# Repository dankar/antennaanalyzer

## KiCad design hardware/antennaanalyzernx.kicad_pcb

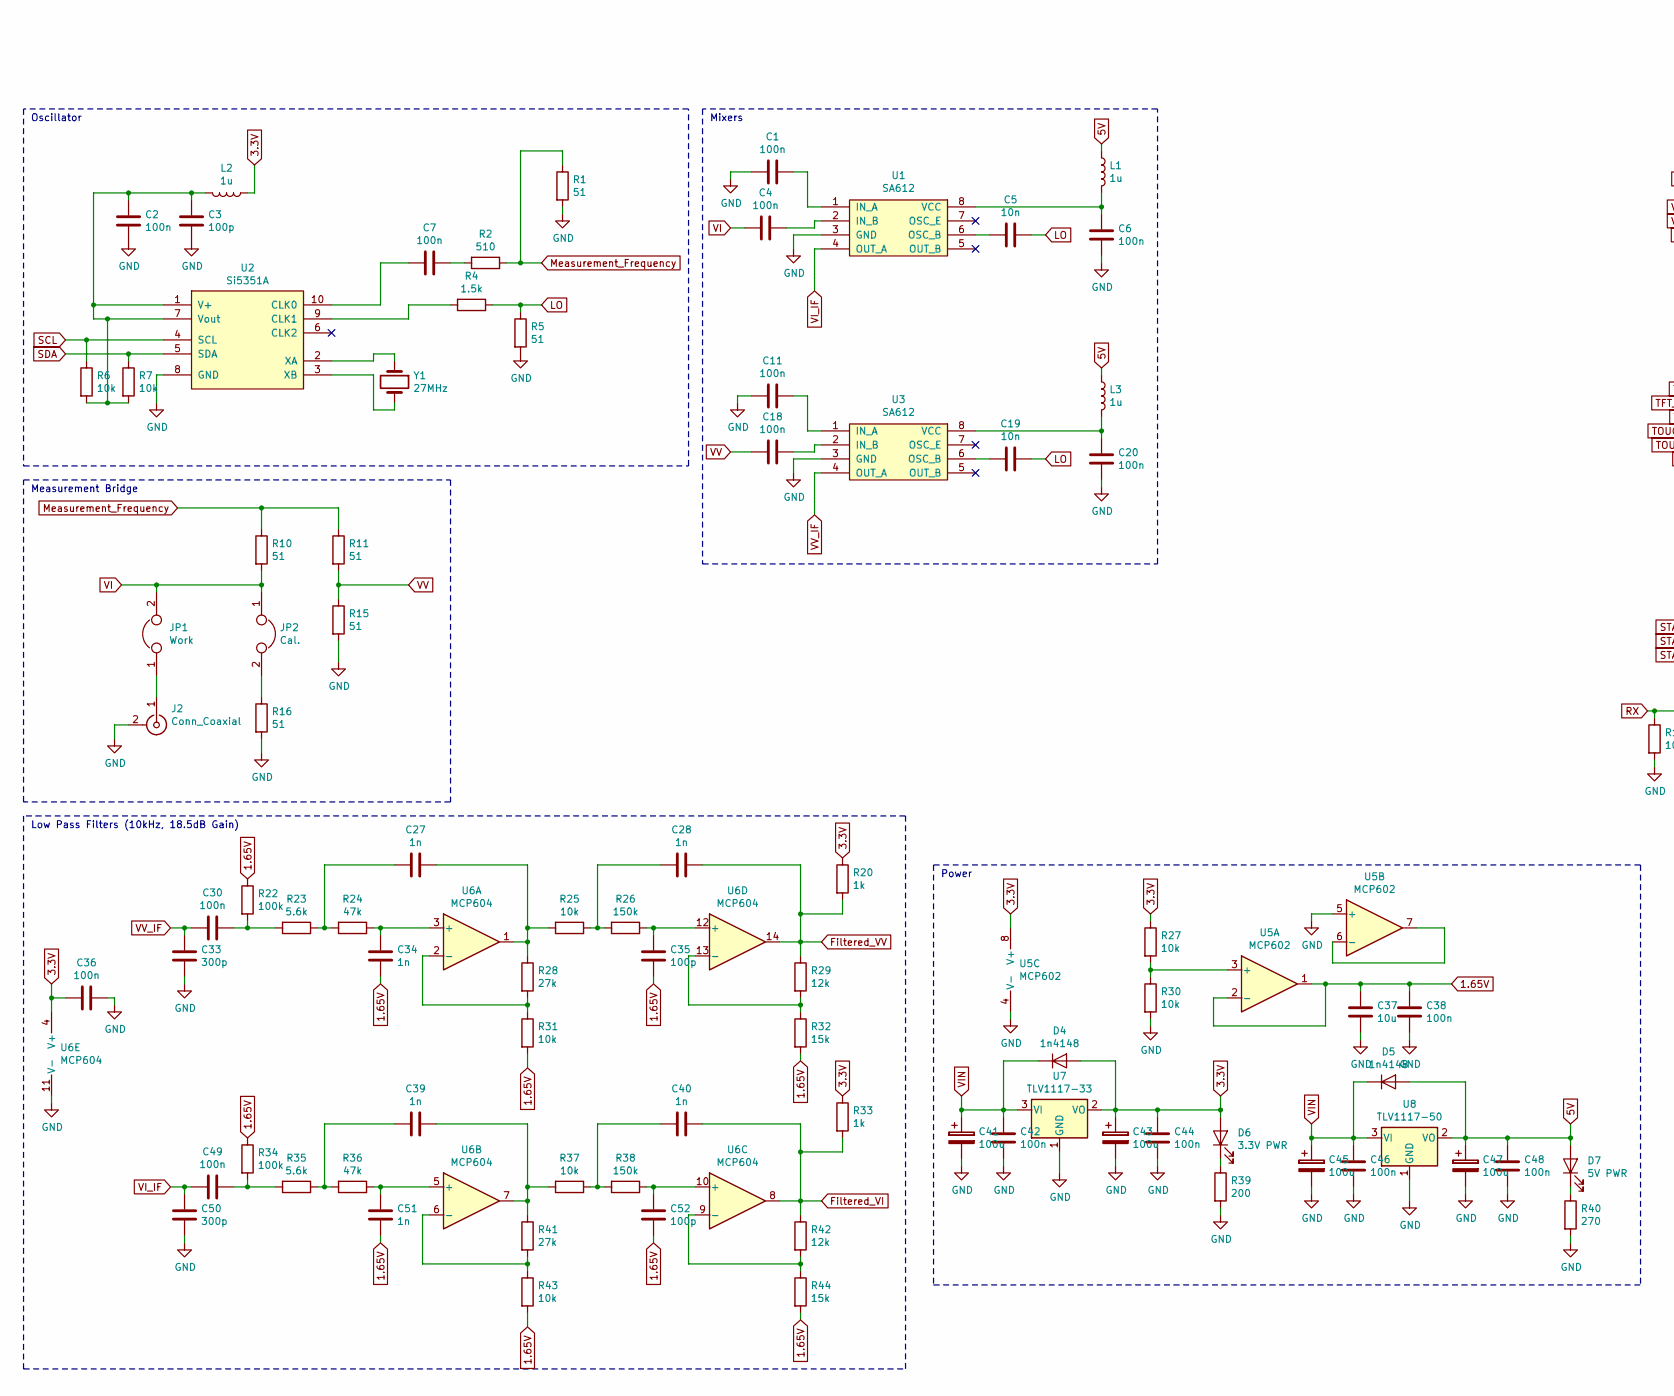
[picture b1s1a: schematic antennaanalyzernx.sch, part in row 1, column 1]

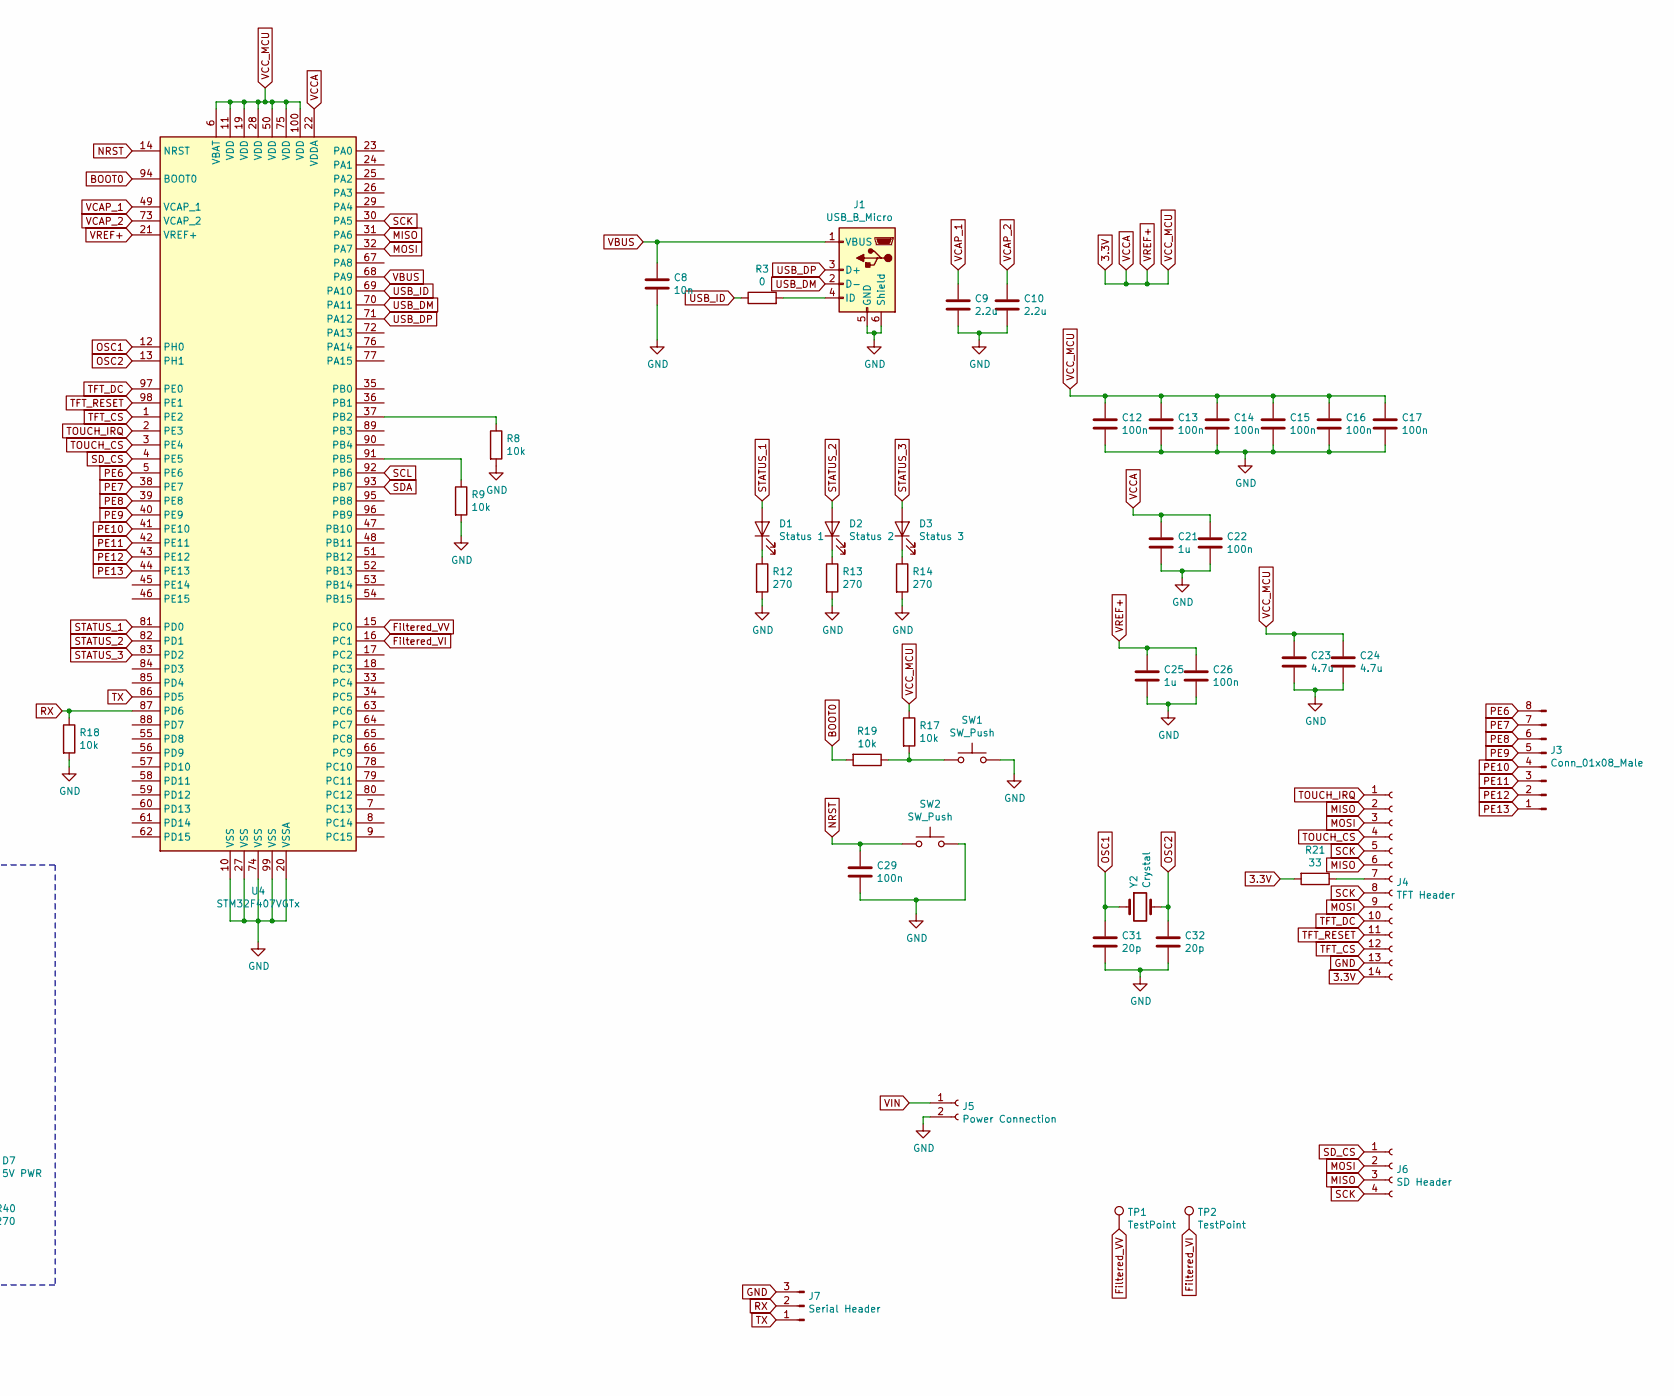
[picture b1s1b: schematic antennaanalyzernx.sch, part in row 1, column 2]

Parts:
C1, C2, C4, C6, C7, C11, C12, C13, C14, C15, C16, C17, C18, C20, C22, C26, C29, C30, C36, C38, C42, C44, C46, C48, C49: 100n; C_0805_HandSoldering
C3, C35, C52: 100p; C_0805_HandSoldering
C5, C8, C19: 10n; C_0805_HandSoldering
C9, C10: 2.2u; C_0805_HandSoldering
C21, C25: 1u; C_0805_HandSoldering
C23, C24: 4.7u; C_0805_HandSoldering
C27, C28, C34, C39, C40, C51: 1n; C_0805_HandSoldering
C31, C32: 20p; C_0805_HandSoldering
C33, C50: 300p; C_0805_HandSoldering
C37: 10u; C_0805_HandSoldering
C41, C43, C45, C47: 100u; CP_Elec_6.3x5.3
D1: Status 1; LED_0805_HandSoldering
D2: Status 2; LED_0805_HandSoldering
D3: Status 3; LED_0805_HandSoldering
D4, D5: 1n4148; D_SOD-323
D6: 3.3V PWR; LED_0805_HandSoldering
D7: 5V PWR; LED_0805_HandSoldering
J1: USB_B_Micro; USB Micro
J2: Conn_Coaxial; CON-SMA-EDGE
J3: Conn_01x08_Male; Pin_Header_Straight_1x08_Pitch2.54mm
J4: TFT Header; Pin_Header_Straight_1x14_Pitch2.54mm
J5: Power Connection; Pin_Header_Straight_1x02_Pitch2.54mm
J6: SD Header; Pin_Header_Straight_1x04_Pitch2.54mm
J7: Serial Header; Pin_Header_Straight_1x03_Pitch2.54mm
JP1: Work; Pin_Header_Straight_1x02_Pitch2.54mm
JP2: Cal.; Pin_Header_Straight_1x02_Pitch2.54mm
L1, L2, L3: 1u; L_1210_HandSoldering
R1, R5, R10, R11, R15, R16: 51; R_0805_HandSoldering
R2: 510; R_0805_HandSoldering
R3: 0; R_0805_HandSoldering
R4: 1.5k; R_0805_HandSoldering
R6, R7, R8, R9, R17, R18, R19, R25, R27, R30, R31, R37, R43: 10k; R_0805_HandSoldering
R12, R13, R14, R40: 270; R_0805_HandSoldering
R20, R33: 1k; R_0805_HandSoldering
R21: 33; R_0805_HandSoldering
R22, R34: 100k; R_0805_HandSoldering
R23, R35: 5.6k; R_0805_HandSoldering
R24, R36: 47k; R_0805_HandSoldering
R26, R38: 150k; R_0805_HandSoldering
R28, R41: 27k; R_0805_HandSoldering
R29, R42: 12k; R_0805_HandSoldering
R32, R44: 15k; R_0805_HandSoldering
R39: 200; R_0805_HandSoldering
SW1, SW2: SW_Push; Switch
TP1, TP2: TestPoint; Measurement_Point_Round-SMD-Pad_Small
U1, U3: SA612; SOIC-8_3.9x4.9mm_Pitch1.27mm
U2: Si5351A; MSOP-10_3x3mm_Pitch0.5mm
U4: STM32F407VGTx; LQFP-100_14x14mm_Pitch0.5mm
U5: MCP602; SOIC-8_3.9x4.9mm_Pitch1.27mm
U6: MCP604; SOIC-14_3.9x8.7mm_Pitch1.27mm
U7: TLV1117-33; SOT-223-3_TabPin2
U8: TLV1117-50; SOT-223-3_TabPin2
Y1: 27MHz; Crystal_HC49-U_Vertical
Y2: Crystal; Crystal_HC49-U_Vertical

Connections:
1.65V: C34.2, C35.2, C37.1, C38.1, C51.2, C52.2, R22.1, R31.2, R32.2, R34.1, R43.2, R44.2, U5.1, U5.2 (-)
3.3V: C12.1, C13.1, C14.1, C15.1, C16.1, C17.1, C21.1, C22.1, C23.1, C24.1, C25.1, C26.1, C36.2, C43.1, C44.1, D4.2 (A), D6.2 (A), J4.14, L2.1, R17.1, R20.1, R21.2, R27.1, R33.1, U4.6 (VBAT), U4.11 (VDD), U4.19 (VDD), U4.21 (VREF+), U4.22 (VDDA), U4.28 (VDD), U4.50 (VDD), U4.75 (VDD), U4.100 (VDD), U5.8 (V+), U6.4 (V+), U7.2 (VO)
5V: C47.1, C48.1, D5.2 (A), D7.2 (A), L1.1, L3.1, U8.2 (VO)
BOOT0: R19.2, U4.94 (BOOT0)
Filtered_VI: C40.1, R33.2, R42.1, TP2.1, U4.16 (PC1), U6.8
Filtered_VV: C28.1, R20.2, R29.1, TP1.1, U4.15 (PC0), U6.14
GND: C1.2, C2.2, C3.2, C6.2, C8.2, C9.2, C10.2, C11.2, C12.2, C13.2, C14.2, C15.2, C16.2, C17.2, C20.2, C21.2, C22.2, C23.2, C24.2, C25.2, C26.2, C29.2, C31.2, C32.2, C33.2, C36.1, C37.2, C38.2, C41.2, C42.2, C43.2, C44.2, C45.2, C46.2, C47.2, C48.2, C50.2, J1.5 (GND), J1.6 (Shield), J2.2 (Ext), J4.13, J5.2, J7.3, R1.2, R5.2, R8.2, R9.2, R12.2, R13.2, R14.2, R15.2, R16.2, R18.2, R30.2, R39.2, R40.2, SW1.2, SW2.2, U1.3 (GND), U2.8 (GND), U3.3 (GND), U4.10 (VSS), U4.20 (VSSA), U4.27 (VSS), U4.74 (VSS), U4.99 (VSS), U5.4 (V-), U5.5 (+), U6.11 (V-), U7.1 (GND), U8.1 (GND)
LO: C5.1, C19.1, R4.1, R5.1
MISO: J4.2, J4.6, J6.3, U4.31 (PA6)
MOSI: J4.3, J4.9, J6.2, U4.32 (PA7)
Measurement_Frequency: R1.1, R2.1, R10.1, R11.1
NRST: C29.1, SW2.1, U4.14 (NRST)
unnamed: C1.1, U1.1 (IN_A)
unnamed: C2.1, C3.1, L2.2, R6.2, R7.2, U2.1 (V+), U2.7 (Vout)
unnamed: C4.1, U1.2 (IN_B)
unnamed: C5.2, U1.6 (OSC_B)
unnamed: C6.1, L1.2, U1.8 (VCC)
unnamed: C7.1, R2.2
unnamed: C7.2, U2.10 (CLK0)
unnamed: C11.1, U3.1 (IN_A)
unnamed: C18.1, U3.2 (IN_B)
unnamed: C19.2, U3.6 (OSC_B)
unnamed: C20.1, L3.2, U3.8 (VCC)
unnamed: C27.1, R25.2, R28.1, U6.1
unnamed: C27.2, R23.1, R24.2
unnamed: C28.2, R25.1, R26.2
unnamed: C30.1, R22.2, R23.2
unnamed: C34.1, R24.1, U6.3 (+)
unnamed: C35.1, R26.1, U6.12 (+)
unnamed: C39.1, R37.2, R41.1, U6.7
unnamed: C39.2, R35.1, R36.2
unnamed: C40.2, R37.1, R38.2
unnamed: C49.1, R34.2, R35.2
unnamed: C51.1, R36.1, U6.5 (+)
unnamed: C52.1, R38.1, U6.10 (+)
unnamed: D1.1 (K), R12.1
unnamed: D2.1 (K), R13.1
unnamed: D3.1 (K), R14.1
unnamed: D6.1 (K), R39.1
unnamed: D7.1 (K), R40.1
unnamed: J1.4 (ID), R3.2
unnamed: J2.1 (In), JP1.1
unnamed: J4.7, R21.1
unnamed: JP2.2, R16.1
unnamed: R4.2, U2.9 (CLK1)
unnamed: R8.1, U4.37 (PB2)
unnamed: R9.1, U4.91 (PB5)
unnamed: R17.2, R19.1, SW1.1
unnamed: R27.2, R30.1, U5.3 (+)
unnamed: R28.2, R31.1, U6.2 (-)
unnamed: R29.2, R32.1, U6.13 (-)
unnamed: R41.2, R43.1, U6.6 (-)
unnamed: R42.2, R44.1, U6.9 (-)
unnamed: U2.2 (XA), Y1.1
unnamed: U2.3 (XB), Y1.2
unnamed: U5.6 (-), U5.7
OSC1: C31.1, U4.12 (PH0), Y2.1
OSC2: C32.1, U4.13 (PH1), Y2.2
PE6: J3.8, U4.5 (PE6)
PE7: J3.7, U4.38 (PE7)
PE8: J3.6, U4.39 (PE8)
PE9: J3.5, U4.40 (PE9)
PE10: J3.4, U4.41 (PE10)
PE11: J3.3, U4.42 (PE11)
PE12: J3.2, U4.43 (PE12)
PE13: J3.1, U4.44 (PE13)
RX: J7.2, R18.1, U4.87 (PD6)
SCK: J4.5, J4.8, J6.4, U4.30 (PA5)
SCL: R6.1, U2.4 (SCL), U4.92 (PB6)
SDA: R7.1, U2.5 (SDA), U4.93 (PB7)
SD_CS: J6.1, U4.4 (PE5)
STATUS_1: D1.2 (A), U4.81 (PD0)
STATUS_2: D2.2 (A), U4.82 (PD1)
STATUS_3: D3.2 (A), U4.83 (PD2)
TFT_CS: J4.12, U4.1 (PE2)
TFT_DC: J4.10, U4.97 (PE0)
TFT_RESET: J4.11, U4.98 (PE1)
TOUCH_CS: J4.4, U4.3 (PE4)
TOUCH_IRQ: J4.1, U4.2 (PE3)
TX: J7.1, U4.86 (PD5)
USB_DM: J1.2 (D-), U4.70 (PA11)
USB_DP: J1.3 (D+), U4.71 (PA12)
USB_ID: R3.1, U4.69 (PA10)
VBUS: C8.1, J1.1 (VBUS), U4.68 (PA9)
VCAP_1: C9.1, U4.49 (VCAP_1)
VCAP_2: C10.1, U4.73 (VCAP_2)
VI: C4.2, JP1.2, JP2.1, R10.2
VIN: C41.1, C42.1, C45.1, C46.1, D4.1 (K), D5.1 (K), J5.1, U7.3 (VI), U8.3 (VI)
VI_IF: C49.2, C50.1, U1.4 (OUT_A)
VV: C18.2, R11.2, R15.1
VV_IF: C30.2, C33.1, U3.4 (OUT_A)

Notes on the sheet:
Oscillator
Measurement Bridge
Mixers
Low Pass Filters (10kHz, 18.5dB Gain)
Power

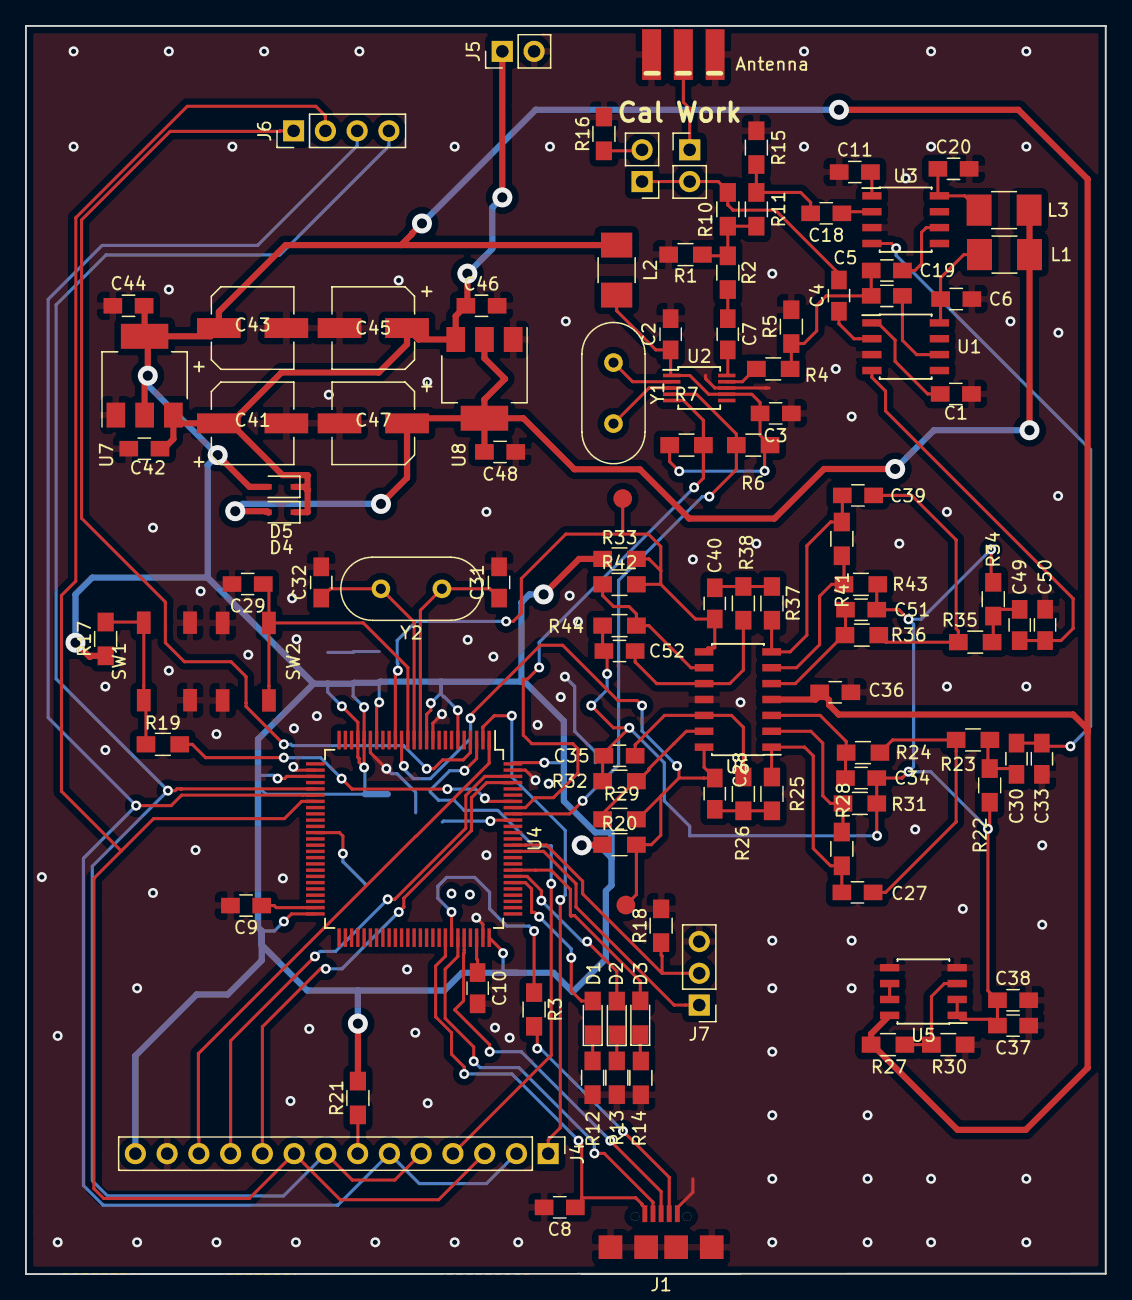
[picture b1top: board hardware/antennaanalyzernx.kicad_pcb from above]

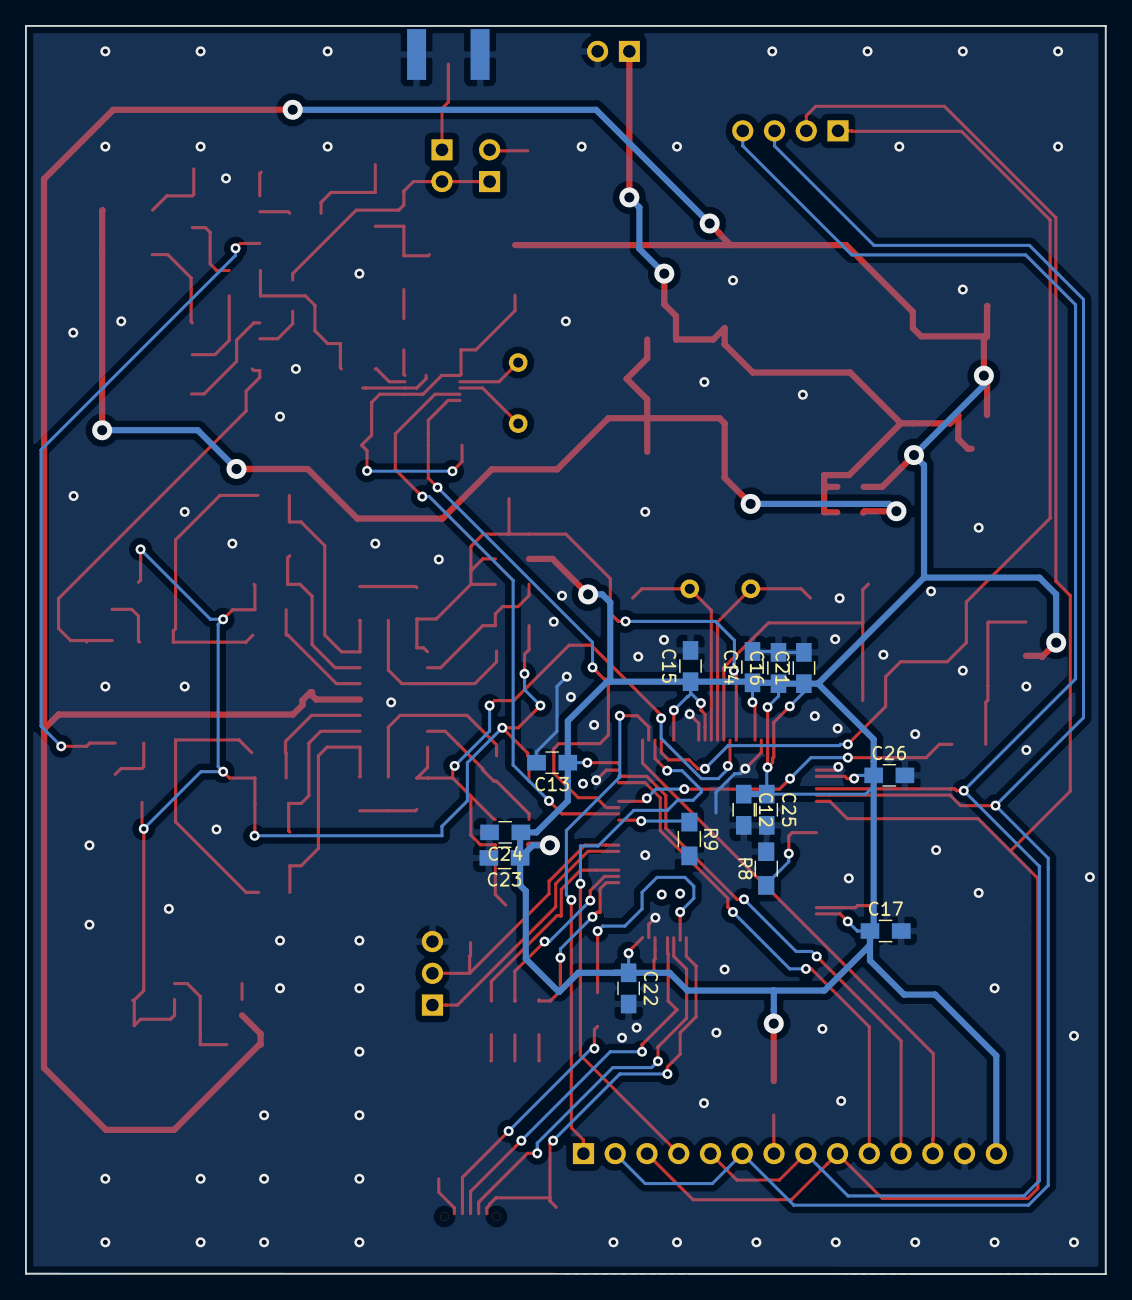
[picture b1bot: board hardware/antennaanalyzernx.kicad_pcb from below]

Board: 2 copper layers, 86.4 x 99.8 mm, 124 parts (14 on the bottom side), 81 nets.

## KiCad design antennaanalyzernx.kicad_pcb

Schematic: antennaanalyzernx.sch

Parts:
C1, C2, C3, C5, C7, C8, C10, C12, C13, C16, C18, C19, C20, C21, C25, C26, C27, C31, C32, C34, C40, C42, C43, C45, C47, C48: 100n; C_0805_HandSoldering
C4, C30, C51: 100p; C_0805_HandSoldering
C6, C17: 10n; C_0805_HandSoldering
C9, C14, C33: 10u; C_0805_HandSoldering
C22: 1u; C_0805_HandSoldering
C23, C24, C29, C37, C38, C50: 1n; C_0805_HandSoldering
C28, C49: 300p; C_0805_HandSoldering
C35, C36: 22p; C_0805_HandSoldering
C39, C41, C44, C46: 100u; CP_Elec_6.3x5.3
D1, D2, D3, D4: 1n4148; D_SOD-323
D5: 3.3V PWR; LED_0805_HandSoldering
D6: 5V PWR; LED_0805_HandSoldering
D7: Status 1; LED_0805_HandSoldering
D8: Status 2; LED_0805_HandSoldering
D9: Status 3; LED_0805_HandSoldering
J1: Power Connection; Molex_KK-6410-02_02x2.54mm_Straight
J2: SPI Header; Molex_KK-6410-04_04x2.54mm_Straight
J3: Serial Header; Molex_KK-6410-06_06x2.54mm_Straight
J4: GPIO; Molex_KK-6410-04_04x2.54mm_Straight
J5: Conn_Coaxial; CON-SMA-EDGE
J6: TFT Connection; Molex_KK-6410-09_09x2.54mm_Straight
J7: Touch Connection; Molex_KK-6410-05_05x2.54mm_Straight
J8: SD Connection; Molex_KK-6410-04_04x2.54mm_Straight
JP1: Work; Pin_Header_Straight_1x02_Pitch2.54mm
JP2: Cal.; Pin_Header_Straight_1x02_Pitch2.54mm
L1, L2, L3, L4: 1u; L_1210_HandSoldering
R1, R3, R6, R8, R9, R10, R19, R21, R24, R25, R30, R34, R37, R39, R40: 10k; R_0805_HandSoldering
R2, R7, R11, R12, R14, R15: 51; R_0805_HandSoldering
R4: 510; R_0805_HandSoldering
R5: 1.5k; R_0805_HandSoldering
R13, R41, R42: 1k; R_0805_HandSoldering
R16, R27: 100k; R_0805_HandSoldering
R17, R28: 5.6k; R_0805_HandSoldering
R18, R29: 47k; R_0805_HandSoldering
R20, R31: 150k; R_0805_HandSoldering
R22, R35: 27k; R_0805_HandSoldering
R23, R36: 12k; R_0805_HandSoldering
R26, R38: 15k; R_0805_HandSoldering
R32: 200; R_0805_HandSoldering
R33, R43, R44, R45: 270; R_0805_HandSoldering
RV1, RV2, RV3: 100k; Potentiometer_Trimmer_Bourns_3266W
SW1: Reset; Switch
TP1: VV Test Point; Measurement_Point_Round-SMD-Pad_Small
TP2, TP3, TP4, TP5: TestPoint; Measurement_Point_Round-SMD-Pad_Small
U1, U4: SA612; SOIC-8_3.9x4.9mm_Pitch1.27mm
U2, U5, U8: LM358; SOIC-8_3.9x4.9mm_Pitch1.27mm
U3: Si5351A; MSOP-10_3x3mm_Pitch0.5mm
U6: 74HC86; SOIC-14_3.9x8.7mm_Pitch1.27mm
U7: 74HC74; SOIC-14_3.9x8.7mm_Pitch1.27mm
U9: LM324; SOIC-14_3.9x8.7mm_Pitch1.27mm
U10: TLV1117-33; SOT-223-3_TabPin2
U11: TLV1117-50; SOT-223-3_TabPin2
U12: ATmega1284P-AU; TQFP-44_10x10mm_Pitch0.8mm
Y1: 27MHz; Crystal_HC49-U_Vertical
Y2: 16MHz; Crystal_HC49-U_Vertical

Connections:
2.5V: C29.2, C30.2, C33.1, C34.1, C50.2, C51.2, R16.1, R25.2, R26.2, R27.1, R37.2, R38.2, U5.2 (-), U5.6 (-), U8.1, U8.2 (-)
3.3V: C41.1, C42.1, D3.2 (A), D5.2 (A), L2.1, U10.2 (VO)
5V: C8.2, C19.2, C20.2, C21.2, C25.1, C32.2, C46.1, C47.1, D4.2 (A), D6.2 (A), J3.3, J6.9, L1.1, L3.1, L4.1, R21.1, R34.2, R41.1, R42.1, U2.8 (V+), U5.8 (V+), U6.14, U7.1, U7.4, U7.10, U7.13, U7.14, U8.8 (V+), U9.4 (V+), U11.2 (VO), U12.5, U12.17, U12.38
CTS: C3.2, C4.2, C5.2, C7.2, C8.1, C9.2, C13.2, C14.2, C18.2, C19.1, C20.1, C21.1, C22.2, C25.2, C27.2, C28.2, C31.2, C32.1, C33.2, C34.2, C35.1, C36.1, C39.2, C40.2, C41.2, C42.2, C44.2, C45.2, C46.2, C47.2, C49.2, J1.2, J3.1, J3.2, J5.2 (Ext), J6.8, R1.1, R2.2, R3.2, R6.1, R7.2, R10.2, R14.2, R15.2, R24.2, R32.2, R33.2, R43.2, R44.2, R45.2, RV1.3, RV2.3, RV3.3, SW1.2, U1.3, U2.4 (V-), U3.8, U4.3, U5.4 (V-), U6.4, U6.5, U6.7, U6.9, U6.10, U6.12, U6.13, U7.7, U7.11, U7.12, U8.4 (V-), U8.5 (+), U9.11 (V-), U10.1 (GND), U11.1 (GND), U12.6, U12.18, U12.28, U12.39
Capacitive_Sign: U7.5, U12.21
DTR: C43.1, J3.6
Filtered_VI: C12.2, C38.1, R36.1, R42.2, TP5.1, U5.5 (+), U9.14
Filtered_VV: C2.2, C24.1, R23.1, R41.2, TP4.1, U5.3 (+), U9.7
GPIO20: J4.1, U12.23
GPIO21: J4.2, U12.24
GPIO22: J4.3, U12.25
GPIO23: J4.4, U12.26
Inductive_Sign: U7.6, U12.22
LO: C6.1, C17.1, R5.1, R7.1
MISO: J2.2, J6.1, J7.2, J8.3, U12.2
MOSI: J2.3, J6.4, J7.3, J8.2, U12.1
Measurement_Frequency: R2.1, R4.1, R11.1, R12.1
unnamed: C1.1, U1.2
unnamed: C2.1, R1.2, R39.2
unnamed: C3.1, C4.1, L2.2, R8.2, R9.2, U3.1, U3.7
unnamed: C5.1, U1.1
unnamed: C6.2, U1.6
unnamed: C7.1, L1.2, U1.8
unnamed: C9.1, D1.1 (K), R3.1, RV1.1, U2.2 (-)
unnamed: C10.1, R4.2
unnamed: C10.2, U3.10
unnamed: C12.1, R6.2, R40.2
unnamed: C13.1, U4.1
unnamed: C14.1, D2.1 (K), R10.1, RV2.1, U2.6 (-)
unnamed: C16.1, U4.2
unnamed: C17.2, U4.6
unnamed: C18.1, L3.2, U4.8
unnamed: C22.1, R13.1, RV3.1
unnamed: C23.1, R19.2, R22.1, U9.1
unnamed: C23.2, R17.1, R18.2
unnamed: C24.2, R19.1, R20.2
unnamed: C26.1, R16.2, R17.2
unnamed: C27.1, L4.2, U12.27
unnamed: C29.1, R18.1, U9.3 (+)
unnamed: C30.1, R20.1, U9.5 (+)
unnamed: C31.1, U12.29
unnamed: C35.2, U12.7, Y2.1
unnamed: C36.2, U12.8, Y2.2
unnamed: C37.1, R30.2, R35.1, U9.8
unnamed: C37.2, R28.1, R29.2
unnamed: C38.2, R30.1, R31.2
unnamed: C48.1, R27.2, R28.2
unnamed: C50.1, R29.1, U9.10 (+)
unnamed: C51.1, R31.1, U9.12 (+)
unnamed: D1.2 (A), U2.1
unnamed: D2.2 (A), U2.7
unnamed: D5.1 (K), R32.1
unnamed: D6.1 (K), R33.1
unnamed: D7.1 (K), R43.1
unnamed: D8.1 (K), R44.1
unnamed: D9.1 (K), R45.1
unnamed: J5.1 (In), JP1.1
unnamed: JP2.2, R15.1
unnamed: R5.2, U3.9
unnamed: R13.2, U6.3
unnamed: R21.2, R24.1, U8.3 (+)
unnamed: R22.2, R25.1, U9.2 (-)
unnamed: R23.2, R26.1, U9.6 (-)
unnamed: R35.2, R37.1, U9.9 (-)
unnamed: R36.2, R38.1, U9.13 (-)
unnamed: R39.1, U2.3 (+)
unnamed: R40.1, U2.5 (+)
unnamed: U3.2, Y1.1
unnamed: U3.3, Y1.2
unnamed: U5.1, U6.1, U7.3
unnamed: U5.7, U6.2, U7.2
unnamed: U8.6 (-), U8.7
Phase: RV3.2, TP3.1, U12.35
RESET: C43.2, J2.4, R34.1, SW1.1, U12.4
RX: J3.4, U12.9
SCK: J2.1, J6.3, J7.5, J8.4, U12.3
SCL: R8.1, U3.4, U12.19
SDA: R9.1, U3.5, U12.20
SD_CS: J8.1, U12.13
STATUS_1: D7.2 (A), U12.14
STATUS_2: D8.2 (A), U12.15
STATUS_3: D9.2 (A), U12.16
TFT_CS: J6.7, U12.42
TFT_DC: J6.5, U12.40
TFT_LED: J6.2, U12.43
TFT_RESET: J6.6, U12.41
TOUCH_CS: J7.4, U12.12
TOUCH_IRQ: J7.1, U12.11
TX: J3.5, U12.10
VI: C1.2, JP1.2, JP2.1, R11.2
VIN: C39.1, C40.1, C44.1, C45.1, D3.1 (K), D4.1 (K), J1.1, U10.3 (VI), U11.3 (VI)
VI_IF: C48.2, C49.1, U1.4
VI_Peak: RV2.2, TP2.1, U12.36
VV: C16.2, R12.2, R14.1
VV_IF: C26.2, C28.1, U4.4
VV_Peak: RV1.2, TP1.1, U12.37

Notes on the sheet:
Oscillator
Measurement Bridge
Mixers
Low Pass Filters (10kHz, 18.5dB Gain)
Peak Detectors
Phase Detector
Connections
Power
MCU

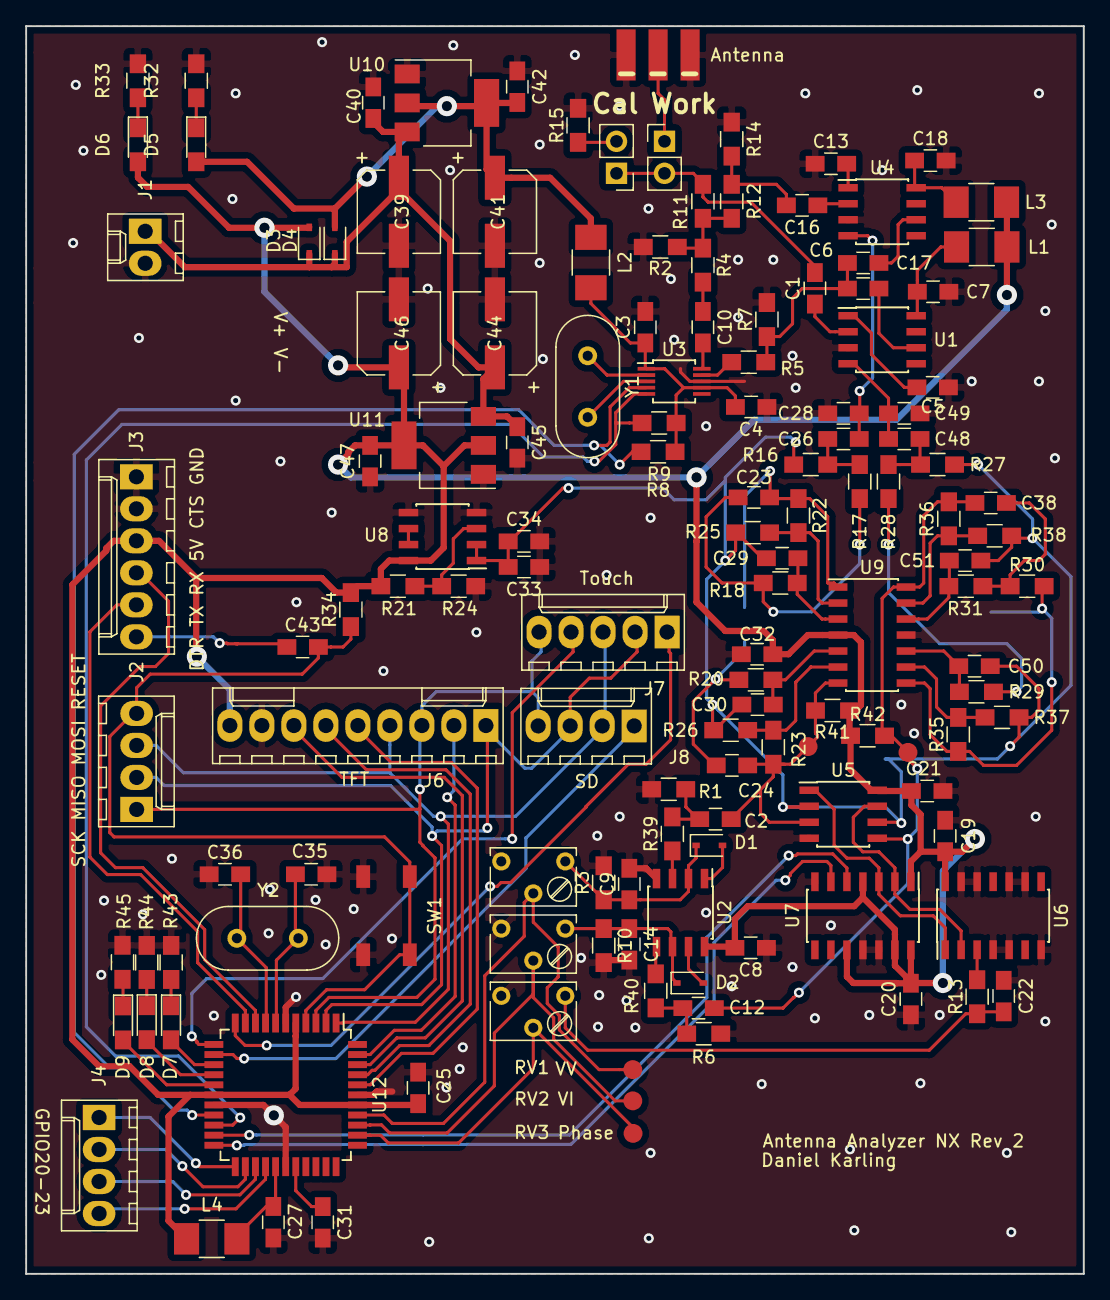
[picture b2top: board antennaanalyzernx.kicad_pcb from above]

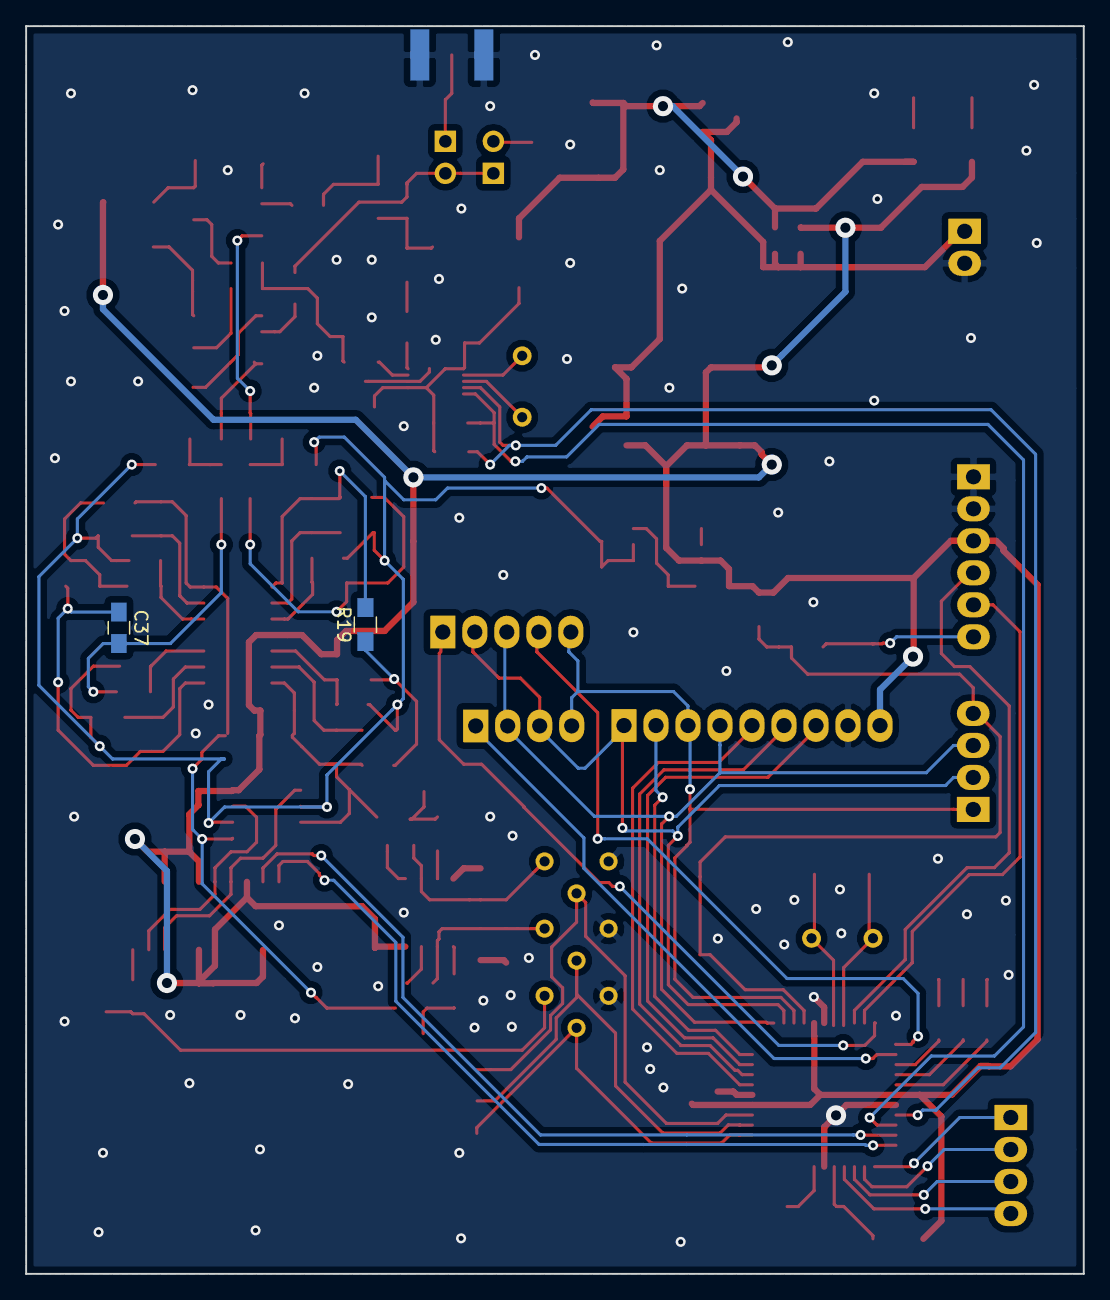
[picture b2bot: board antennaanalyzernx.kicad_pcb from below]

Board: 2 copper layers, 83.9 x 99.0 mm, 140 parts (2 on the bottom side), 96 nets.

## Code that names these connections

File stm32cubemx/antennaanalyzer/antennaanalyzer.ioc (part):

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Mcu.Name=STM32F407V(E-G)Tx
Mcu.Package=LQFP100
Mcu.UserName=STM32F407VGTx
PA11.Mode=Device_Only
PA11.Signal=USB_OTG_FS_DM
PA12.Mode=Device_Only
PA12.Signal=USB_OTG_FS_DP
PA5.Mode=Full_Duplex_Master
PA5.Signal=SPI1_SCK
PA6.Mode=Full_Duplex_Master
PA6.Signal=SPI1_MISO
PA7.Mode=Full_Duplex_Master
PA7.Signal=SPI1_MOSI
PA9.Mode=Activate_VBUS
PA9.Signal=USB_OTG_FS_VBUS
PB6.Mode=I2C
PB6.Signal=I2C1_SCL
PB7.Mode=I2C
PB7.Signal=I2C1_SDA
PC0.GPIOParameters=GPIO_Label
PC0.GPIO_Label=FILTERERD_VV
PC0.Signal=ADCx_IN10
PC1.GPIOParameters=GPIO_Label
PC1.GPIO_Label=FILTERED_VI
PC1.Signal=ADCx_IN11
PD0.GPIOParameters=GPIO_Speed,PinState,GPIO_PuPd,GPIO_Label,GPIO_ModeDefaultOutputPP
PD0.GPIO_Label=STATUS_LED1
PD0.GPIO_ModeDefaultOutputPP=GPIO_MODE_OUTPUT_PP
PD0.GPIO_PuPd=GPIO_PULLUP
PD0.GPIO_Speed=GPIO_SPEED_FREQ_HIGH
PD0.PinState=GPIO_PIN_SET
PD0.Signal=GPIO_Output
PD1.GPIOParameters=GPIO_Speed,GPIO_PuPd,GPIO_Label
PD1.GPIO_Label=STATUS_LED2
PD1.GPIO_PuPd=GPIO_PULLUP
PD1.GPIO_Speed=GPIO_SPEED_FREQ_HIGH
PD1.Signal=GPIO_Output
PD2.GPIOParameters=GPIO_Speed,PinState,GPIO_PuPd,GPIO_Label
PD2.GPIO_Label=STATUS_LED3
PD2.GPIO_PuPd=GPIO_PULLUP
PD2.GPIO_Speed=GPIO_SPEED_FREQ_HIGH
PD2.PinState=GPIO_PIN_RESET
PD2.Signal=GPIO_Output
PE0.GPIOParameters=GPIO_Speed,GPIO_Label
PE0.GPIO_Label=TFT_DC
PE0.GPIO_Speed=GPIO_SPEED_FREQ_VERY_HIGH
PE0.Signal=GPIO_Output
PE1.GPIOParameters=GPIO_Speed,GPIO_Label
PE1.GPIO_Label=TFT_RESET
PE1.GPIO_Speed=GPIO_SPEED_FREQ_VERY_HIGH
PE1.Signal=GPIO_Output
PE2.GPIOParameters=GPIO_Speed,GPIO_Label
PE2.GPIO_Label=TFT_CS
PE2.GPIO_Speed=GPIO_SPEED_FREQ_VERY_HIGH
PE2.Signal=GPIO_Output
PE3.GPIOParameters=GPIO_Label
PE3.GPIO_Label=TOUCH_IRQ
PE3.Signal=GPIO_Input
PE4.GPIOParameters=GPIO_Speed,GPIO_PuPd,GPIO_Label
PE4.GPIO_Label=TOUCH_CS
PE4.GPIO_PuPd=GPIO_NOPULL
PE4.GPIO_Speed=GPIO_SPEED_FREQ_VERY_HIGH
PE4.Signal=GPIO_Output
PE5.GPIOParameters=GPIO_Speed,GPIO_Label
PE5.GPIO_Label=SD_CS
PE5.GPIO_Speed=GPIO_SPEED_FREQ_VERY_HIGH
PE5.Signal=GPIO_Output
PH0-OSC_IN.Mode=HSE-External-Oscillator
PH0-OSC_IN.Signal=RCC_OSC_IN
PH1-OSC_OUT.Mode=HSE-External-Oscillator
PH1-OSC_OUT.Signal=RCC_OSC_OUT
RCC.HSE_VALUE=8000000
RCC.SYSCLKFreq_VALUE=168000000
RCC.SYSCLKSource=RCC_SYSCLKSOURCE_PLLCLK
board=custom

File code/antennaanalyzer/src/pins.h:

#pragma once

#define VV_PIN A0
#define VI_PIN A1
#define PHASE_PIN A2

#define TFT_DC	        0 // PB0 
#define TFT_RESET	    1 // PB1
#define TFT_CS	        2 // PB2
#define TFT_LED	        3 // PB3
#define MOSI	        5 // PB5
#define MISO	        6 // PB6
#define SCK		        7 // PB7
#define CAPACITIVE_PIN	18 // PC2
#define INDUCTIVE_PIN	19 // PC3
#define TOUCH_IRQ	    10 // PD2
#define TOUCH_CS	    11 // PD3
#define SD_CS	        12 // PD4

#define STATUS1_PIN 13
#define STATUS2_PIN 14
#define STATUS3_PIN 15

#define GPIO20      20
#define GPIO21      21
#define GPIO22      22
#define GPIO23      23

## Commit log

2018-11-30 Initial
2018-12-01 Refactoring
2018-12-01 More refactoring
2018-12-01 Fixed bug using incorrect frequency during calibration
2018-12-01 Moved folders
2018-12-01 Some paint here, some paint there...
2018-12-01 Added menu system and brightness controls
2018-12-01 Improvements...
2018-12-02 Added interpolation of calibration coefficients
2019-02-24 stm32 version
2019-06-27 Regions for swr graph and frequencyt readout
2019-08-15 Removed arduino version
